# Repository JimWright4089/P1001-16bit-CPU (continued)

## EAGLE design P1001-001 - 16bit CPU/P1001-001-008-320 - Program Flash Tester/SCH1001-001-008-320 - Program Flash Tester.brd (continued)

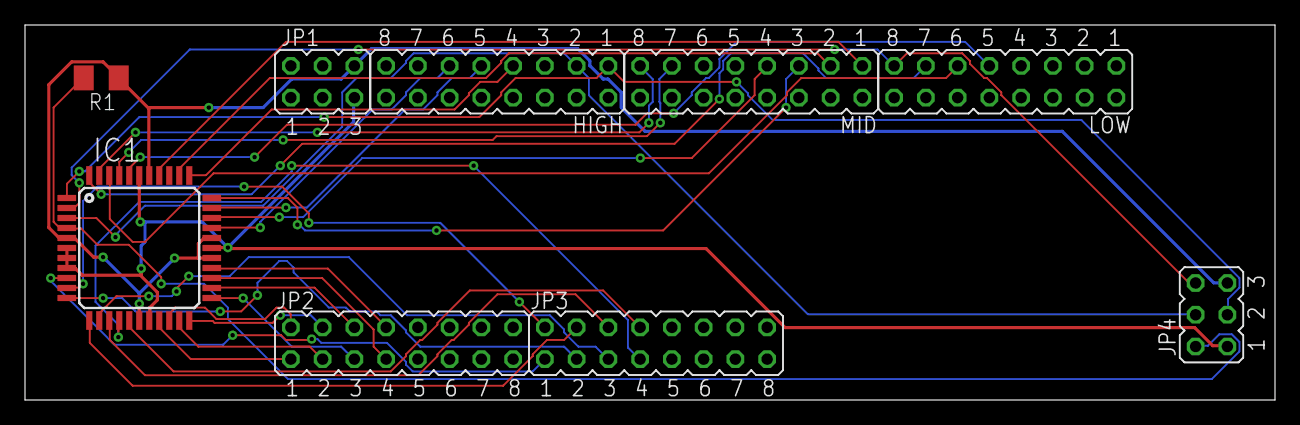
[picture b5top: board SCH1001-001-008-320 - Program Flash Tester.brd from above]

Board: 2 copper layers, 100.0 x 30.0 mm, 9 parts (0 on the bottom side), 34 nets.

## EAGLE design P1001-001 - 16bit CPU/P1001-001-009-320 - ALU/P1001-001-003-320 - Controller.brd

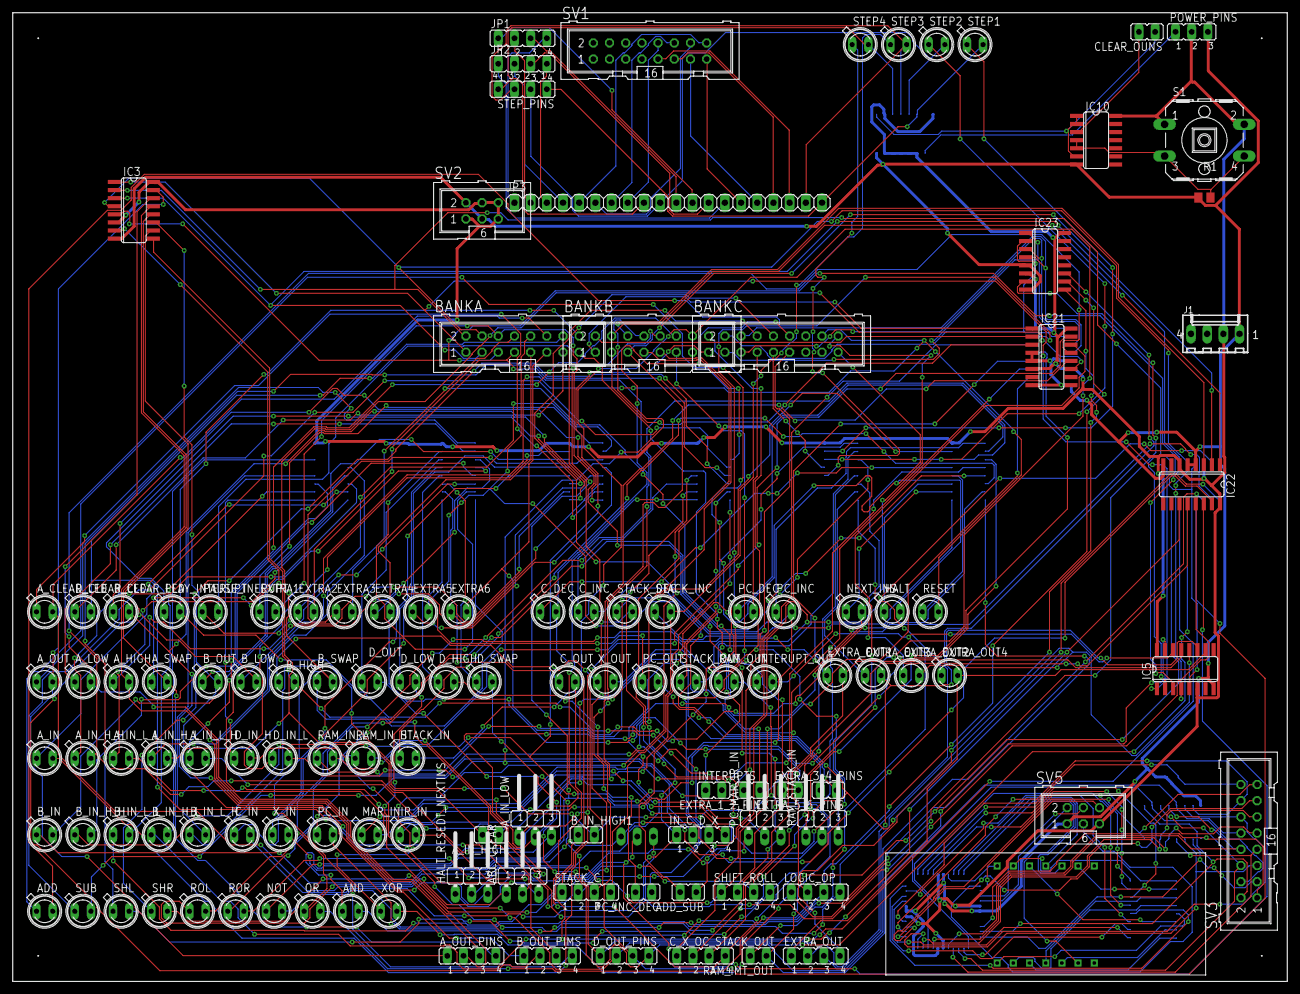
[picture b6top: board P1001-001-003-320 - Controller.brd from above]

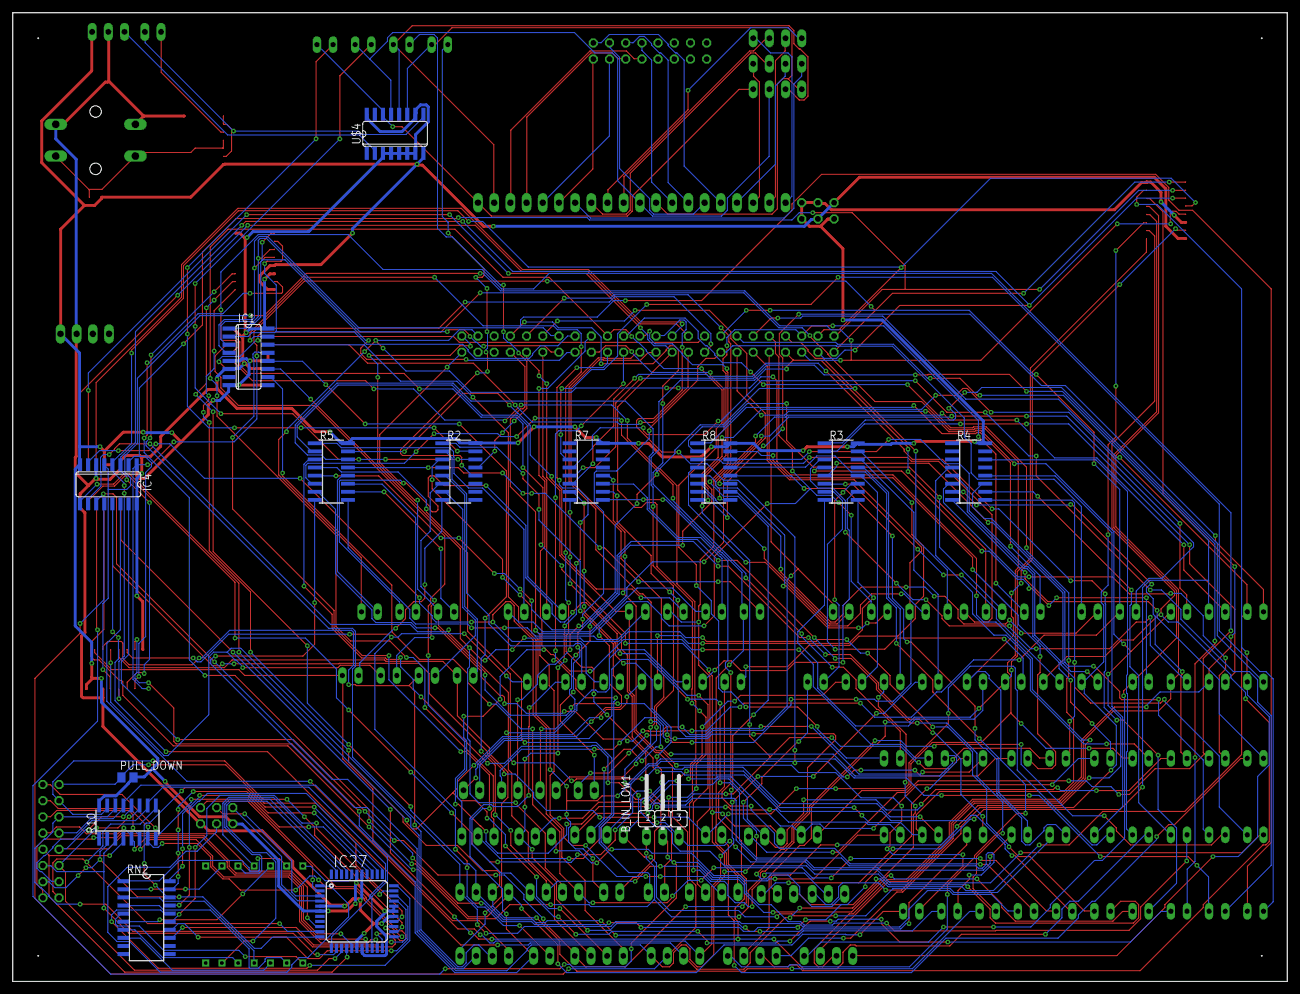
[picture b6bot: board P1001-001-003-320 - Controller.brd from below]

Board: 2 copper layers, 200.0 x 152.0 mm, 136 parts (14 on the bottom side), 229 nets.

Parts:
ABC_CLEAR: JP2W
ADD: SFH482
ADD_SUB: JP1
AND: SFH482
A_CLEAR_LED: SFH482
A_HIGH: SFH482
A_IN: SFH482
A_IN_HIGH: JP1
A_IN_H_H: SFH482
A_IN_H_L: SFH482
A_IN_LOW: JP2W
A_IN_L_H: SFH482
A_IN_L_L: SFH482
A_LOW: SFH482
A_OUT: SFH482
A_OUT_PINS: JP4
A_SWAP: SFH482
BANKA: ML16
BANKB: ML16
BANKC: ML16
B_CLEAR_LED: SFH482
B_HIGH: SFH482
B_IN: SFH482
B_IN_HIGH1: JP1
B_IN_H_H: SFH482
B_IN_H_L: SFH482
B_IN_LOW1: JP2W
B_IN_L_H: SFH482
B_IN_L_L: SFH482
B_LOW: SFH482
B_OUT: SFH482
B_OUT_PIMS: JP4
B_SWAP: SFH482
CLEAR_OUNS: JP1
C_DEC: SFH482
C_IN: SFH482
C_INC: SFH482
C_OUT: SFH482
C_X_OC_STACK_OUT: JP4
D_CLEAR_LED: SFH482
D_HIGH: SFH482
D_IN_H: SFH482
D_IN_L: SFH482
D_LOW: SFH482
D_OUT: SFH482
D_OUT_PINS: JP4
D_SWAP: SFH482
EXTRA1, EXTRA2, EXTRA3, EXTRA4, EXTRA5, EXTRA6: SFH482
EXTRA_1_2_PINS, EXTRA_3_4_PINS, EXTRA_5_6_PINS: JP1
EXTRA_OUT: JP4
EXTRA_OUT1, EXTRA_OUT2, EXTRA_OUT3, EXTRA_OUT4: SFH482
HALT: SFH482
HALT_RESEDT_NEXTINS: JP2W
IC1, IC3, IC4, IC5, IC21, IC22, IC23: 74LS138D; SO16
IC10: 74ALS00D; SO14
IC27: MEGA8535-A; TQFP44
INTERUPTS: JP1
INTERUPT_OUT: SFH482
IN_C_D_X: JP4
IR_IN: SFH482
J1: 22-27-2041-04; 6410-04
JP1, JP2: JP4
JP3: 1X20
LOGIC_OP: JP4
MAR_IN: SFH482
NEXT_INS: SFH482
NOT: SFH482
OR: SFH482
PAUSE_INERUPT: SFH482
PC_DEC: SFH482
PC_IN: SFH482
PC_INC: SFH482
PC_INC_DEC: JP1
PC_MAR_IR_IN: JP2W
PC_OUT: SFH482
PLAY_INTERUPT: SFH482
POWER_PINS: JP2
PULL_DOWN: M0805
R1: M0805
R2, R3, R4, R5, R7, R8, R10: SO16
RAM_IMT_OUT: JP1
RAM_IN_H: SFH482
RAM_IN_L: SFH482
RAM_OUT: SFH482
RAM_STACK_IN: JP2W
RESET: SFH482
RN2: SOMC20
ROL: SFH482
ROR: SFH482
S1: B3F-40XX
SHIFT_ROLL: JP4
SHL: SFH482
SHR: SFH482
STACK_C: JP4
STACK_DEC: SFH482
STACK_IN: SFH482
STACK_INC: SFH482
STACK_OUT: SFH482
STEP1, STEP2, STEP3, STEP4: SFH482
STEP_PINS: JP4
SUB: SFH482
SV1, SV3: ML16
SV2, SV5: ML6
U$1: 4-DIGIT-7-SEGMENT
U$4: SN74HC161; SO16
XOR: SFH482
X_IN: SFH482
X_OUT: SFH482

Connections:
!CLEAR: CLEAR_OUNS.1, IC10.1, IC10.2, IC10.6, U$4.9
A: IC27.37, RN2.20
B: IC27.36, RN2.19
C: IC27.35, RN2.18
CLEAR: CLEAR_OUNS.2, IC10.3
CLK: POWER_PINS.1, U$4.2
D: IC27.34, RN2.17
DATAA0: BANKA.1, IC3.1, IC4.1, IC5.1
DATAA1: BANKA.2, IC3.2, IC4.2, IC5.2
DATAA2: BANKA.3, IC3.3, IC4.3, IC5.3
DATAA3: BANKA.4, IC3.4, IC4.4, IC5.4
DATAA4: BANKA.5, IC3.5, IC4.5, IC5.5
DATAA5: BANKA.6, EXTRA1.K, EXTRA_1_2_PINS.1
DATAA6: BANKA.7, EXTRA2.K, EXTRA_1_2_PINS.2
DATAA7: BANKA.8, EXTRA3.K, EXTRA_3_4_PINS.1
DATAA8: BANKA.9, EXTRA4.K, EXTRA_3_4_PINS.2
DATAA9: BANKA.10, EXTRA5.K, EXTRA_5_6_PINS.1
DATAA10: BANKA.11, EXTRA6.K, EXTRA_5_6_PINS.2
DATAA11: ABC_CLEAR.1, A_CLEAR_LED.K, BANKA.12
DATAA12: ABC_CLEAR.2, BANKA.13, B_CLEAR_LED.K
DATAA13: ABC_CLEAR.3, BANKA.14, D_CLEAR_LED.K
DATAA14: BANKA.15, INTERUPTS.1, PAUSE_INERUPT.K
DATAA15: BANKA.16, INTERUPTS.2, PLAY_INTERUPT.K
DATAB0: BANKB.1, IC21.1
DATAB1: BANKB.2, IC21.2
DATAB2: BANKB.3, IC21.3
DATAB3: BANKB.4, IC22.1
DATAB4: BANKB.5, IC22.2, PC_INC_DEC.2
DATAB5: BANKB.6, IC22.3
DATAB6: BANKB.7, C_IN.K, IN_C_D_X.1
DATAB7: BANKB.8, D_IN_L.K, IN_C_D_X.2
DATAB8: BANKB.9, D_IN_H.K, IN_C_D_X.3
DATAB9: BANKB.10, IN_C_D_X.4, X_IN.K
DATAB10: BANKB.11, IR_IN.K, PC_MAR_IR_IN.1
DATAB11: BANKB.12, MAR_IN.K, PC_MAR_IR_IN.2
DATAB12: BANKB.13, PC_IN.K, PC_MAR_IR_IN.3
DATAB13: BANKB.14, RAM_STACK_IN.1, STACK_IN.K
DATAB14: BANKB.15, RAM_IN_L.K, RAM_STACK_IN.2
DATAB15: BANKB.16, RAM_IN_H.K, RAM_STACK_IN.3
DATAC0: BANKC.1, IC1.1, IC23.1
DATAC1: BANKC.2, IC1.2, IC23.2
DATAC2: BANKC.3, IC1.3, IC23.3
DATAC3: BANKC.4, IC1.4, IC23.4
DATAC4: BANKC.5, PC_DEC.K
DATAC5: BANKC.6, PC_INC.K, PC_INC_DEC.1
DATAC6: BANKC.7, STACK_C.4, STACK_INC.K
DATAC7: BANKC.8, STACK_C.3, STACK_DEC.K
DATAC8: BANKC.9, C_INC.K, STACK_C.2
DATAC9: BANKC.10, C_DEC.K, STACK_C.1
DATAC13: BANKC.14, HALT_RESEDT_NEXTINS.3, RESET.K
DATAC14: BANKC.15, HALT.K, HALT_RESEDT_NEXTINS.2
DATAC15: BANKC.16, HALT_RESEDT_NEXTINS.1, NEXT_INS.K
DIG0: IC27.40, U$1.PIN14
DIG1: IC27.41, U$1.PIN11
DIG2: IC27.42, U$1.PIN10
DIG3: IC27.43, U$1.PIN6
DP: IC27.30, RN2.13
E: IC27.33, RN2.16
EXTERN_BUS0: IC27.9, R10.1, SV3.1
EXTERN_BUS1: IC27.10, R10.9, SV3.2
EXTERN_BUS2: IC27.11, R10.2, SV3.3
EXTERN_BUS3: IC27.12, R10.10, SV3.4
EXTERN_BUS4: IC27.13, R10.3, SV3.5
EXTERN_BUS5: IC27.14, R10.11, SV3.6
EXTERN_BUS6: IC27.15, R10.4, SV3.7
EXTERN_BUS7: IC27.16, R10.12, SV3.8
EXTERN_BUS8: IC27.19, R10.5, SV3.9
EXTERN_BUS9: IC27.20, R10.13, SV3.10
EXTERN_BUS10: IC27.21, R10.6, SV3.11
EXTERN_BUS11: IC27.22, R10.14, SV3.12
EXTERN_BUS12: IC27.23, R10.7, SV3.13
EXTERN_BUS13: IC27.24, R10.15, SV3.14
EXTERN_BUS14: IC27.25, R10.8, SV3.15
EXTERN_BUS15: IC27.26, PULL_DOWN.1, SV3.16
F: IC27.32, RN2.15
G: IC27.31, RN2.14
GND: IC1.5, IC1.8, IC3.8, IC4.8, IC5.8, IC10.7, IC21.4, IC21.5, IC21.8, IC22.4, IC22.5, IC22.8, IC23.5, IC23.8, IC27.6, IC27.18, IC27.28, IC27.29, IC27.39, J1.1, POWER_PINS.3, PULL_DOWN.2, R1.1, R10.16, SV2.2, SV2.3, SV5.1, U$4.8
IN_BUS0: JP3.20, STEP1.K, STEP_PINS.1, U$4.14
IN_BUS1: JP3.10, STEP2.K, STEP_PINS.2, U$4.13
IN_BUS2: JP3.19, STEP3.K, STEP_PINS.3, U$4.12
IN_BUS3: JP3.9, STEP4.K, STEP_PINS.4, U$4.11
IN_BUS4: JP3.18, SV1.9
IN_BUS5: JP3.8, SV1.10
IN_BUS6: JP3.17, SV1.11
IN_BUS7: JP3.7, SV1.12
IN_BUS8: JP3.16, SV1.13
IN_BUS9: JP3.6, SV1.14
IN_BUS10: JP3.15, SV1.15
IN_BUS11: JP3.5, SV1.16
IN_BUS12: JP2.1, JP3.14
IN_BUS13: JP2.2, JP3.4
IN_BUS14: JP2.3, JP3.13
IN_BUS15: JP2.4, JP3.3
IN_BUS16: JP1.1, JP3.12
IN_BUS17: JP1.2, JP3.2
IN_BUS18: JP1.3, JP3.11
IN_BUS19: JP1.4, JP3.1
unnamed: IC10.4, IC10.5, R1.2, S1.3, S1.4
unnamed: EXTRA1.A, R8.1
unnamed: EXTRA2.A, R8.2
unnamed: R8.13, X_IN.A
unnamed: EXTRA4.A, R8.4
unnamed: EXTRA3.A, R8.3
unnamed: EXTRA6.A, R8.6
unnamed: B_CLEAR_LED.A, R8.8
unnamed: A_CLEAR_LED.A, R8.7
unnamed: D_CLEAR_LED.A, R8.9
unnamed: PAUSE_INERUPT.A, R8.10
unnamed: PLAY_INTERUPT.A, R8.11
unnamed: C_IN.A, R8.12
unnamed: D_IN_L.A, R8.15
unnamed: D_IN_H.A, R8.14
unnamed: PC_INC.A, R5.1
unnamed: PC_DEC.A, R5.2
unnamed: IR_IN.A, R5.3
unnamed: MAR_IN.A, R5.4
unnamed: PC_IN.A, R5.5
unnamed: R5.6, STACK_IN.A
unnamed: R5.7, RAM_IN_L.A
unnamed: R5.8, RAM_IN_H.A
unnamed: NEXT_INS.A, R5.10
unnamed: R5.15, STACK_DEC.A
unnamed: C_INC.A, R5.14
unnamed: C_DEC.A, R5.13
unnamed: R5.12, RESET.A
unnamed: HALT.A, R5.11
unnamed: R5.9, STACK_INC.A
unnamed: A_IN.K, A_IN_LOW.1, IC21.15
unnamed: A_IN_LOW.2, A_IN_L_L.K, IC21.14
unnamed: A_IN_H_H.K, A_IN_LOW.3, IC21.13
unnamed: A_IN_HIGH.1, A_IN_L_H.K, IC21.12
unnamed: A_IN_HIGH.2, A_IN_H_L.K, IC21.11
unnamed: A_IN.A, R4.8
unnamed: A_IN_L_L.A, R4.7
unnamed: A_IN_H_H.A, R4.6
unnamed: A_IN_L_H.A, R4.5
unnamed: A_IN_H_L.A, R4.4
unnamed: EXTRA5.A, R8.5
unnamed: B_IN.A, B_IN_LOW1.3, IC22.15
unnamed: B_IN_LOW1.2, B_IN_L_L.A, IC22.14
unnamed: B_IN_H_H.A, B_IN_LOW1.1, IC22.13
unnamed: B_IN_HIGH1.2, B_IN_L_H.A, IC22.12
unnamed: B_IN_HIGH1.1, B_IN_H_L.A, IC22.11
unnamed: B_IN.K, R4.9
unnamed: B_IN_L_L.K, R4.10
unnamed: B_IN_H_H.K, R4.11
unnamed: B_IN_L_H.K, R4.12
unnamed: B_IN_H_L.K, R4.14
unnamed: R7.8, ROR.A
unnamed: R7.7, ROL.A
unnamed: R7.6, SHR.A
unnamed: R7.5, SHL.A
unnamed: R7.4, SUB.A
unnamed: ADD.A, R7.3
unnamed: ADD.K, ADD_SUB.2, IC1.15
unnamed: ADD_SUB.1, IC1.14, SUB.K
unnamed: IC1.13, SHIFT_ROLL.4, SHL.K
unnamed: IC1.12, SHIFT_ROLL.3, SHR.K
unnamed: IC1.11, ROL.K, SHIFT_ROLL.2
unnamed: IC1.10, ROR.K, SHIFT_ROLL.1
unnamed: NOT.A, R7.9
unnamed: AND.A, R7.10
unnamed: OR.A, R7.11
unnamed: R7.12, XOR.A
unnamed: IC23.7, LOGIC_OP.1, XOR.K
unnamed: IC23.9, LOGIC_OP.2, OR.K
unnamed: AND.K, IC23.10, LOGIC_OP.3
unnamed: IC23.11, LOGIC_OP.4, NOT.K
unnamed: A_OUT.K, A_OUT_PINS.1, IC3.15
unnamed: A_LOW.K, A_OUT_PINS.2, IC3.14
unnamed: A_HIGH.K, A_OUT_PINS.3, IC3.13
unnamed: A_OUT_PINS.4, A_SWAP.K, IC3.12
unnamed: B_OUT.K, B_OUT_PIMS.1, IC3.11
unnamed: B_LOW.K, B_OUT_PIMS.2, IC3.10
unnamed: B_HIGH.K, B_OUT_PIMS.3, IC3.9
unnamed: B_OUT_PIMS.4, B_SWAP.K, IC3.7
unnamed: D_OUT.K, D_OUT_PINS.1, IC4.14
unnamed: C_OUT.K, C_X_OC_STACK_OUT.4, IC4.15
unnamed: D_LOW.K, D_OUT_PINS.2, IC4.13
unnamed: D_HIGH.K, D_OUT_PINS.3, IC4.12
unnamed: D_OUT_PINS.4, D_SWAP.K, IC4.11
unnamed: C_X_OC_STACK_OUT.3, IC4.10, X_OUT.K
unnamed: C_X_OC_STACK_OUT.2, IC4.9, PC_OUT.K
unnamed: C_X_OC_STACK_OUT.1, IC4.7, STACK_OUT.K
unnamed: A_OUT.A, R3.1
unnamed: A_LOW.A, R3.2
unnamed: A_HIGH.A, R3.3
unnamed: A_SWAP.A, R3.4
unnamed: B_OUT.A, R3.5
unnamed: B_LOW.A, R3.6
unnamed: B_HIGH.A, R3.7
unnamed: B_SWAP.A, R3.8
unnamed: C_OUT.A, R3.15
unnamed: D_OUT.A, R3.14
unnamed: D_LOW.A, R3.13
unnamed: D_HIGH.A, R3.12
unnamed: D_SWAP.A, R3.11
unnamed: R3.10, X_OUT.A
unnamed: PC_OUT.A, R3.9
unnamed: IC5.15, RAM_IMT_OUT.1, RAM_OUT.K
unnamed: IC5.14, INTERUPT_OUT.K, RAM_IMT_OUT.2
unnamed: EXTRA_OUT.4, EXTRA_OUT1.K, IC5.13
unnamed: EXTRA_OUT.3, EXTRA_OUT2.K, IC5.12
unnamed: EXTRA_OUT.2, EXTRA_OUT3.K, IC5.11
unnamed: EXTRA_OUT.1, EXTRA_OUT4.K, IC5.10
unnamed: R2.1, STACK_OUT.A
unnamed: EXTRA_OUT4.A, R2.8
unnamed: EXTRA_OUT3.A, R2.7
unnamed: EXTRA_OUT2.A, R2.6
unnamed: EXTRA_OUT1.A, R2.5
unnamed: R2.2, RAM_OUT.A
unnamed: INTERUPT_OUT.A, R2.3
unnamed: IC27.1, SV5.3
unnamed: IC27.3, SV5.4
unnamed: IC27.2, SV5.6
unnamed: IC27.4, SV5.2
unnamed: RN2.1, U$1.PIN13
unnamed: RN2.2, U$1.PIN9
unnamed: RN2.3, U$1.PIN4
unnamed: RN2.4, U$1.PIN2
unnamed: RN2.5, U$1.PIN1
unnamed: RN2.6, U$1.PIN12
unnamed: RN2.7, U$1.PIN5
unnamed: RN2.8, U$1.PIN3
unnamed: R2.15, STEP1.A
unnamed: R2.14, STEP2.A
unnamed: R2.13, STEP3.A
unnamed: R2.12, STEP4.A
VCC: IC1.6, IC1.16, IC3.6, IC3.16, IC4.6, IC4.16, IC5.6, IC5.16, IC10.14, IC21.6, IC21.16, IC22.6, IC22.16, IC23.6, IC23.16, IC27.5, IC27.17, IC27.27, IC27.38, J1.2, POWER_PINS.2, R2.16, R3.16, R4.16, R5.16, R7.16, R8.16, S1.1, S1.2, SV2.1, SV2.4, SV2.5, SV2.6, SV5.5, U$4.3, U$4.4, U$4.5, U$4.6, U$4.7, U$4.10, U$4.16

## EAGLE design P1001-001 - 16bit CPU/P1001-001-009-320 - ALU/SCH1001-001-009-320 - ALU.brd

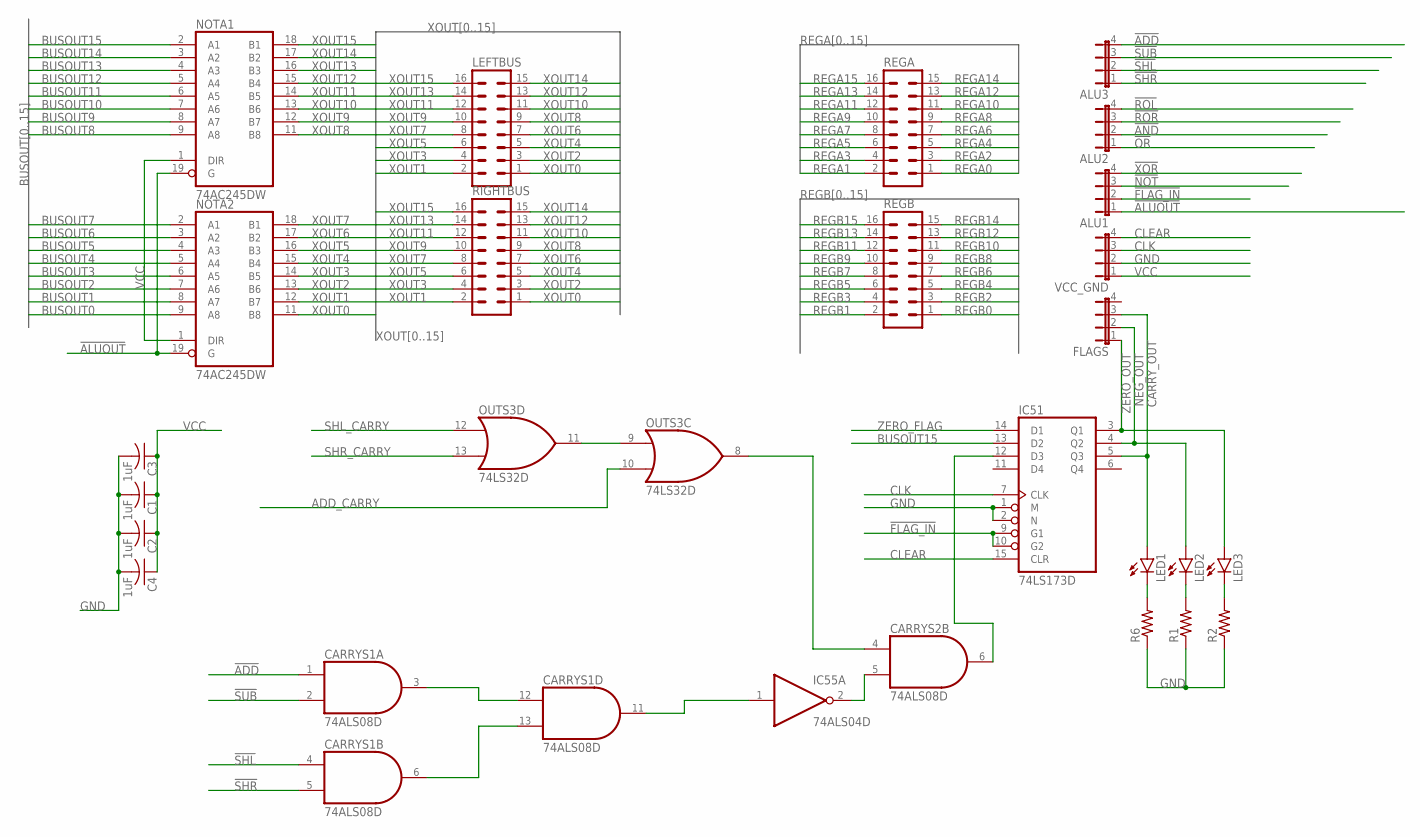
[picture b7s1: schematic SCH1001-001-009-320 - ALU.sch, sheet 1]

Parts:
ALU1, ALU2, ALU3: JP4E; JP4
C1, C2, C3, C4: 1uF; C1206
CARRYS1, CARRYS2: 74ALS08D; SO14
FLAGS: JP4E; JP4
IC51: 74LS173D; SO16
IC55: 74ALS04D; SO14
LED1, LED2, LED3: LED5MM
LEFTBUS: ML16
NOTA1, NOTA2: 74AC245DW; SO20W
OUTS3: 74LS32D; SO14
R1, R2, R6: R-US_M1206; M1206
REGA: ML16
REGB: ML16
RIGHTBUS: ML16
VCC_GND: JP4E; JP4

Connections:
!ADD: ALU3.4, CARRYS1.1 (I0); also elsewhere on the board
!ALUOUT: ALU1.1, NOTA1.19 (G), NOTA2.19 (G)
!AND: ALU2.2; also elsewhere on the board
!FLAG_IN: ALU1.2, IC51.9 (G1), IC51.10 (G2)
!NOT: ALU1.3; also elsewhere on the board
!OR: ALU2.1; also elsewhere on the board
!ROL: ALU2.4
!ROR: ALU2.3
!SHL: ALU3.2, CARRYS1.4 (I0); also elsewhere on the board
!SHR: ALU3.1, CARRYS1.5 (I1); also elsewhere on the board
!SUB: ALU3.3, CARRYS1.2 (I1); also elsewhere on the board
!XOR: ALU1.4; also elsewhere on the board
ADD_CARRY: OUTS3.10 (I1); also elsewhere on the board
BUSOUT0: NOTA2.9 (A8); also elsewhere on the board
BUSOUT1: NOTA2.8 (A7); also elsewhere on the board
BUSOUT2: NOTA2.7 (A6); also elsewhere on the board
BUSOUT3: NOTA2.6 (A5); also elsewhere on the board
BUSOUT4: NOTA2.5 (A4); also elsewhere on the board
BUSOUT5: NOTA2.4 (A3); also elsewhere on the board
BUSOUT6: NOTA2.3 (A2); also elsewhere on the board
BUSOUT7: NOTA2.2 (A1); also elsewhere on the board
BUSOUT8: NOTA1.9 (A8); also elsewhere on the board
BUSOUT9: NOTA1.8 (A7); also elsewhere on the board
BUSOUT10: NOTA1.7 (A6); also elsewhere on the board
BUSOUT11: NOTA1.6 (A5); also elsewhere on the board
BUSOUT12: NOTA1.5 (A4); also elsewhere on the board
BUSOUT13: NOTA1.4 (A3); also elsewhere on the board
BUSOUT14: NOTA1.3 (A2); also elsewhere on the board
BUSOUT15: IC51.13 (D2), NOTA1.2 (A1); also elsewhere on the board
CARRY_OUT: FLAGS.3, IC51.5 (Q3), LED1.A
CLEAR: IC51.15 (CLR), VCC_GND.4
CLK: IC51.7 (CLK), VCC_GND.3
GND: C1.2, C2.2, C3.2, C4.2, CARRYS1.7 (GND), CARRYS2.7 (GND), IC51.1 (M), IC51.2 (N), IC51.8 (GND), IC55.7 (GND), NOTA1.10 (GND), NOTA2.10 (GND), OUTS3.7 (GND), R1.1, R2.1, R6.1, VCC_GND.2; also elsewhere on the board
unnamed: OUTS3.9 (I0), OUTS3.11 (O)
unnamed: CARRYS2.4 (I0), OUTS3.8 (O)
unnamed: CARRYS2.6 (O), IC51.12 (D3)
unnamed: CARRYS2.5 (I1), IC55.2 (O)
unnamed: CARRYS1.11 (O), IC55.1 (I)
unnamed: CARRYS1.3 (O), CARRYS1.12 (I0)
unnamed: CARRYS1.6 (O), CARRYS1.13 (I1)
unnamed: LED1.K (C), R6.2
unnamed: LED2.K (C), R1.2
unnamed: LED3.K (C), R2.2
NEG_OUT: FLAGS.2, IC51.4 (Q2), LED2.A
REGA0: REGA.1; also elsewhere on the board
REGA1: REGA.2; also elsewhere on the board
REGA2: REGA.3; also elsewhere on the board
REGA3: REGA.4; also elsewhere on the board
REGA4: REGA.5; also elsewhere on the board
REGA5: REGA.6; also elsewhere on the board
REGA6: REGA.7; also elsewhere on the board
REGA7: REGA.8; also elsewhere on the board
REGA8: REGA.9; also elsewhere on the board
REGA9: REGA.10; also elsewhere on the board
REGA10: REGA.11; also elsewhere on the board
REGA11: REGA.12; also elsewhere on the board
REGA12: REGA.13; also elsewhere on the board
REGA13: REGA.14; also elsewhere on the board
REGA14: REGA.15; also elsewhere on the board
REGA15: REGA.16; also elsewhere on the board
REGB0: REGB.1; also elsewhere on the board
REGB1: REGB.2; also elsewhere on the board
REGB2: REGB.3; also elsewhere on the board
REGB3: REGB.4; also elsewhere on the board
REGB4: REGB.5; also elsewhere on the board
REGB5: REGB.6; also elsewhere on the board
REGB6: REGB.7; also elsewhere on the board
REGB7: REGB.8; also elsewhere on the board
REGB8: REGB.9; also elsewhere on the board
REGB9: REGB.10; also elsewhere on the board
REGB10: REGB.11; also elsewhere on the board
REGB11: REGB.12; also elsewhere on the board
REGB12: REGB.13; also elsewhere on the board
REGB13: REGB.14; also elsewhere on the board
REGB14: REGB.15; also elsewhere on the board
REGB15: REGB.16; also elsewhere on the board
SHL_CARRY: OUTS3.12 (I0); also elsewhere on the board
SHR_CARRY: OUTS3.13 (I1); also elsewhere on the board
VCC: C1.1, C2.1, C3.1, C4.1, CARRYS1.14 (VCC), CARRYS2.14 (VCC), IC51.16 (VCC), IC55.14 (VCC), NOTA1.1 (DIR), NOTA1.20 (VCC), NOTA2.1 (DIR), NOTA2.20 (VCC), OUTS3.14 (VCC), VCC_GND.1; also elsewhere on the board
XOUT0: LEFTBUS.1, NOTA2.11 (B8), RIGHTBUS.1
XOUT1: LEFTBUS.2, NOTA2.12 (B7), RIGHTBUS.2
XOUT2: LEFTBUS.3, NOTA2.13 (B6), RIGHTBUS.3
XOUT3: LEFTBUS.4, NOTA2.14 (B5), RIGHTBUS.4
XOUT4: LEFTBUS.5, NOTA2.15 (B4), RIGHTBUS.5
XOUT5: LEFTBUS.6, NOTA2.16 (B3), RIGHTBUS.6
XOUT6: LEFTBUS.7, NOTA2.17 (B2), RIGHTBUS.7
XOUT7: LEFTBUS.8, NOTA2.18 (B1), RIGHTBUS.8
XOUT8: LEFTBUS.9, NOTA1.11 (B8), RIGHTBUS.9
XOUT9: LEFTBUS.10, NOTA1.12 (B7), RIGHTBUS.10
XOUT10: LEFTBUS.11, NOTA1.13 (B6), RIGHTBUS.11
XOUT11: LEFTBUS.12, NOTA1.14 (B5), RIGHTBUS.12
XOUT12: LEFTBUS.13, NOTA1.15 (B4), RIGHTBUS.13
XOUT13: LEFTBUS.14, NOTA1.16 (B3), RIGHTBUS.14
XOUT14: LEFTBUS.15, NOTA1.17 (B2), RIGHTBUS.15
XOUT15: LEFTBUS.16, NOTA1.18 (B1), RIGHTBUS.16
ZERO_FLAG: IC51.14 (D1); also elsewhere on the board
ZERO_OUT: FLAGS.1, IC51.3 (Q1), LED3.A

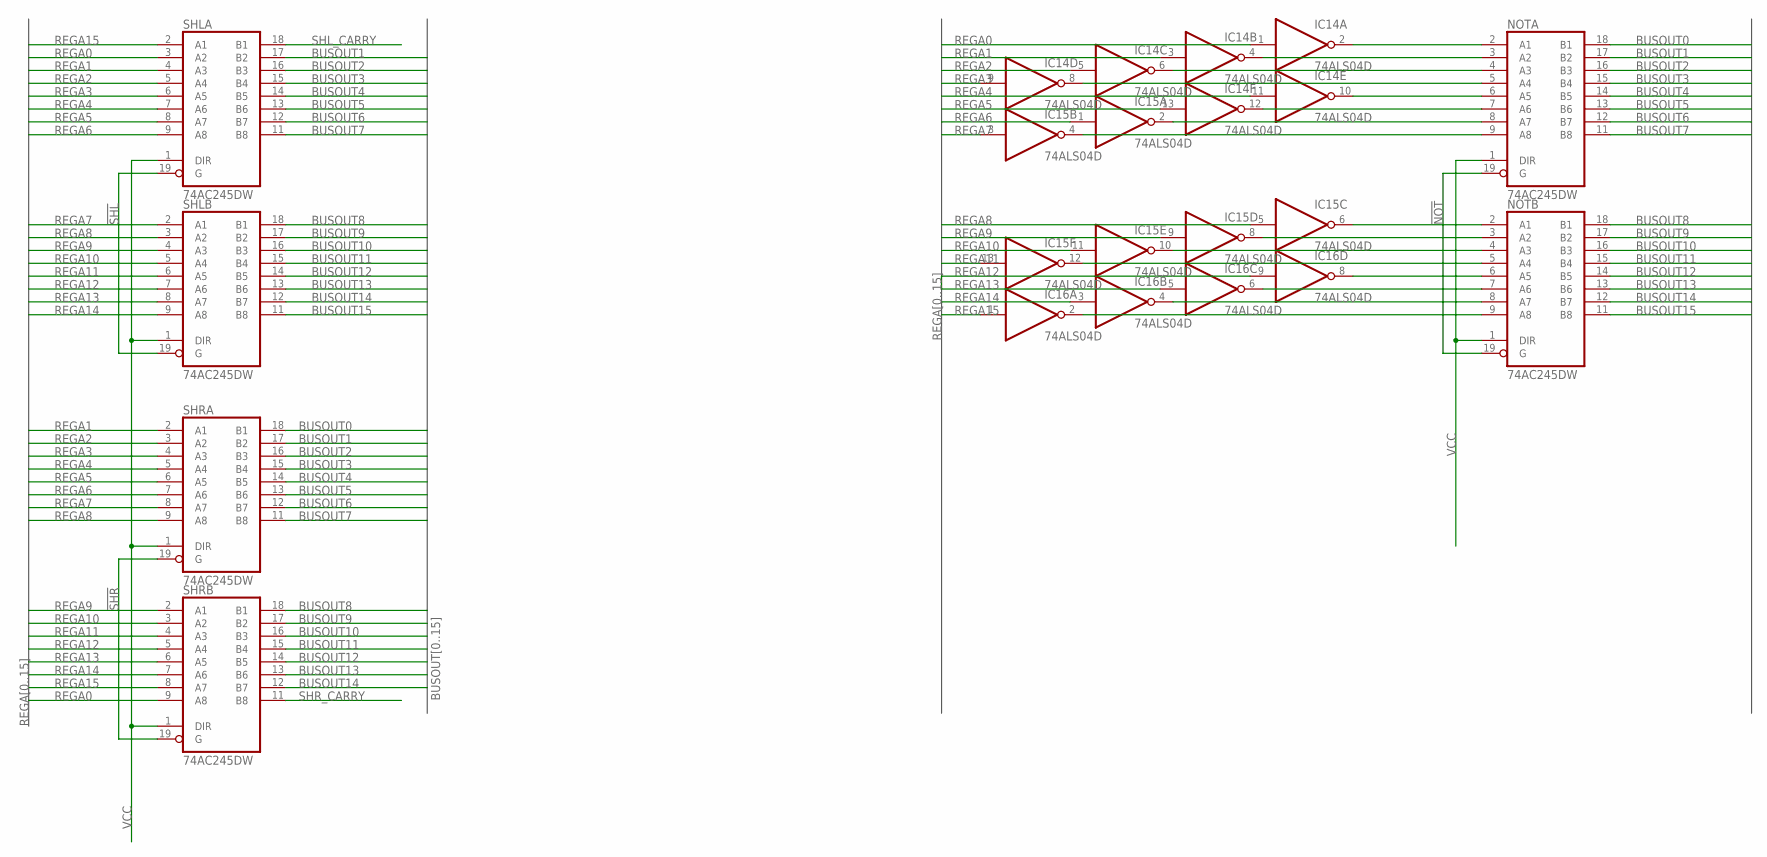
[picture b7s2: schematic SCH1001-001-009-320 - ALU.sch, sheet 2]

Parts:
IC14, IC15, IC16: 74ALS04D; SO14
NOTA: 74AC245DW; SO20W
NOTB: 74AC245DW; SO20W
SHLA: 74AC245DW; SO20W
SHLB: 74AC245DW; SO20W
SHRA: 74AC245DW; SO20W
SHRB: 74AC245DW; SO20W

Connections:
!NOT: NOTA.19 (G), NOTB.19 (G); also elsewhere on the board
!SHL: SHLA.19 (G), SHLB.19 (G); also elsewhere on the board
!SHR: SHRA.19 (G), SHRB.19 (G); also elsewhere on the board
BUSOUT0: NOTA.18 (B1), SHRA.18 (B1); also elsewhere on the board
BUSOUT1: NOTA.17 (B2), SHLA.17 (B2), SHRA.17 (B2); also elsewhere on the board
BUSOUT2: NOTA.16 (B3), SHLA.16 (B3), SHRA.16 (B3); also elsewhere on the board
BUSOUT3: NOTA.15 (B4), SHLA.15 (B4), SHRA.15 (B4); also elsewhere on the board
BUSOUT4: NOTA.14 (B5), SHLA.14 (B5), SHRA.14 (B5); also elsewhere on the board
BUSOUT5: NOTA.13 (B6), SHLA.13 (B6), SHRA.13 (B6); also elsewhere on the board
BUSOUT6: NOTA.12 (B7), SHLA.12 (B7), SHRA.12 (B7); also elsewhere on the board
BUSOUT7: NOTA.11 (B8), SHLA.11 (B8), SHRA.11 (B8); also elsewhere on the board
BUSOUT8: NOTB.18 (B1), SHLB.18 (B1), SHRB.18 (B1); also elsewhere on the board
BUSOUT9: NOTB.17 (B2), SHLB.17 (B2), SHRB.17 (B2); also elsewhere on the board
BUSOUT10: NOTB.16 (B3), SHLB.16 (B3), SHRB.16 (B3); also elsewhere on the board
BUSOUT11: NOTB.15 (B4), SHLB.15 (B4), SHRB.15 (B4); also elsewhere on the board
BUSOUT12: NOTB.14 (B5), SHLB.14 (B5), SHRB.14 (B5); also elsewhere on the board
BUSOUT13: NOTB.13 (B6), SHLB.13 (B6), SHRB.13 (B6); also elsewhere on the board
BUSOUT14: NOTB.12 (B7), SHLB.12 (B7), SHRB.12 (B7); also elsewhere on the board
BUSOUT15: NOTB.11 (B8), SHLB.11 (B8); also elsewhere on the board
GND: IC14.7 (GND), IC15.7 (GND), IC16.7 (GND), NOTA.10 (GND), NOTB.10 (GND), SHLA.10 (GND), SHLB.10 (GND), SHRA.10 (GND), SHRB.10 (GND); also elsewhere on the board
unnamed: IC14.2 (O), NOTA.2 (A1)
unnamed: IC14.10 (O), NOTA.6 (A5)
unnamed: IC14.4 (O), NOTA.3 (A2)
unnamed: IC14.12 (O), NOTA.7 (A6)
unnamed: IC15.2 (O), NOTA.8 (A7)
unnamed: IC14.6 (O), NOTA.4 (A3)
unnamed: IC14.8 (O), NOTA.5 (A4)
unnamed: IC15.4 (O), NOTA.9 (A8)
unnamed: IC15.6 (O), NOTB.2 (A1)
unnamed: IC16.8 (O), NOTB.6 (A5)
unnamed: IC15.8 (O), NOTB.3 (A2)
unnamed: IC16.6 (O), NOTB.7 (A6)
unnamed: IC16.4 (O), NOTB.8 (A7)
unnamed: IC15.10 (O), NOTB.4 (A3)
unnamed: IC15.12 (O), NOTB.5 (A4)
unnamed: IC16.2 (O), NOTB.9 (A8)
REGA0: IC14.1 (I), SHLA.3 (A2), SHRB.9 (A8); also elsewhere on the board
REGA1: IC14.3 (I), SHLA.4 (A3), SHRA.2 (A1); also elsewhere on the board
REGA2: IC14.5 (I), SHLA.5 (A4), SHRA.3 (A2); also elsewhere on the board
REGA3: IC14.9 (I), SHLA.6 (A5), SHRA.4 (A3); also elsewhere on the board
REGA4: IC14.11 (I), SHLA.7 (A6), SHRA.5 (A4); also elsewhere on the board
REGA5: IC14.13 (I), SHLA.8 (A7), SHRA.6 (A5); also elsewhere on the board
REGA6: IC15.1 (I), SHLA.9 (A8), SHRA.7 (A6); also elsewhere on the board
REGA7: IC15.3 (I), SHLB.2 (A1), SHRA.8 (A7); also elsewhere on the board
REGA8: IC15.5 (I), SHLB.3 (A2), SHRA.9 (A8); also elsewhere on the board
REGA9: IC15.9 (I), SHLB.4 (A3), SHRB.2 (A1); also elsewhere on the board
REGA10: IC15.11 (I), SHLB.5 (A4), SHRB.3 (A2); also elsewhere on the board
REGA11: IC15.13 (I), SHLB.6 (A5), SHRB.4 (A3); also elsewhere on the board
REGA12: IC16.9 (I), SHLB.7 (A6), SHRB.5 (A4); also elsewhere on the board
REGA13: IC16.5 (I), SHLB.8 (A7), SHRB.6 (A5); also elsewhere on the board
REGA14: IC16.3 (I), SHLB.9 (A8), SHRB.7 (A6); also elsewhere on the board
REGA15: IC16.1 (I), SHLA.2 (A1), SHRB.8 (A7); also elsewhere on the board
SHL_CARRY: SHLA.18 (B1); also elsewhere on the board
SHR_CARRY: SHRB.11 (B8); also elsewhere on the board
VCC: IC14.14 (VCC), IC15.14 (VCC), IC16.14 (VCC), NOTA.1 (DIR), NOTA.20 (VCC), NOTB.1 (DIR), NOTB.20 (VCC), SHLA.1 (DIR), SHLA.20 (VCC), SHLB.1 (DIR), SHLB.20 (VCC), SHRA.1 (DIR), SHRA.20 (VCC), SHRB.1 (DIR), SHRB.20 (VCC); also elsewhere on the board
